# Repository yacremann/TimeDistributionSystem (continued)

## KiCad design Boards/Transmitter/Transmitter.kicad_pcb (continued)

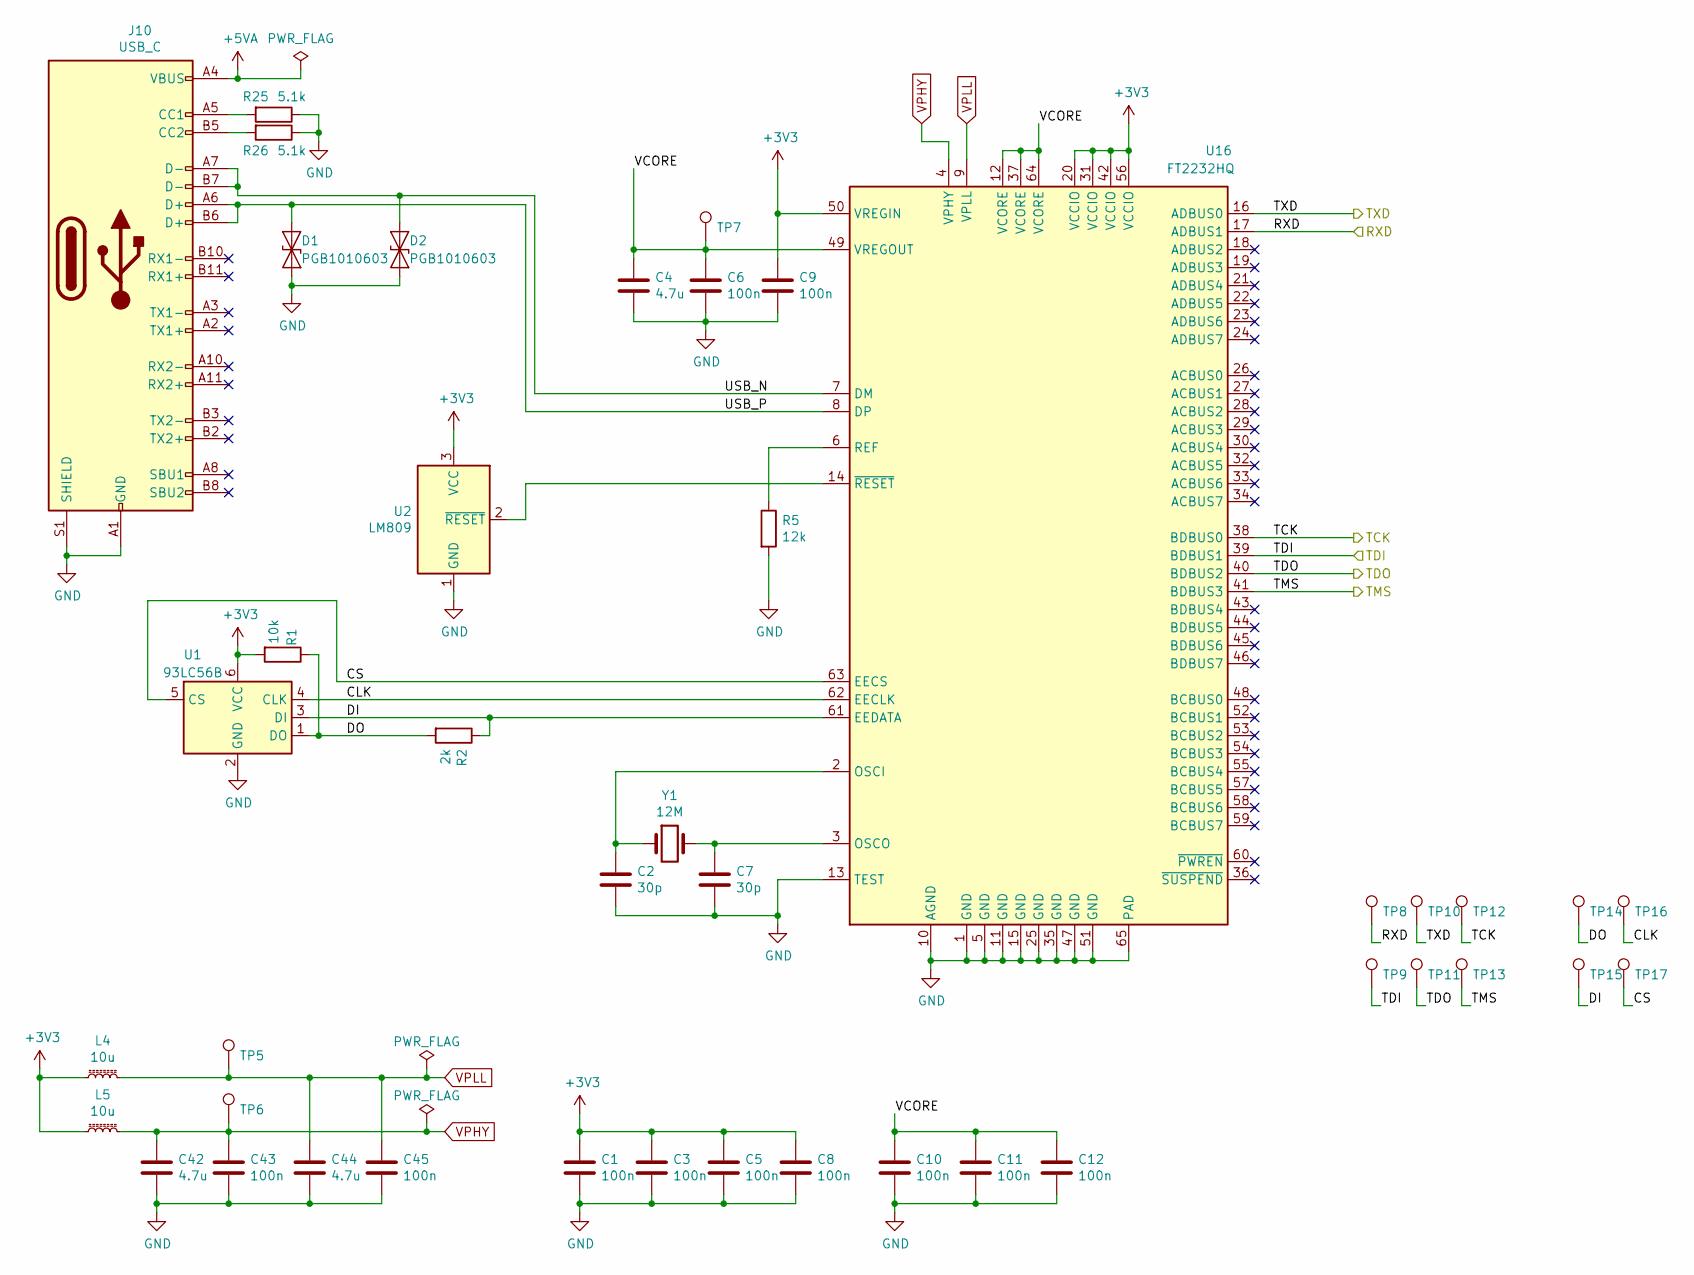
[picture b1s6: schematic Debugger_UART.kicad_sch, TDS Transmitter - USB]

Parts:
C1, C3, C5, C6, C8, C9, C10, C11, C12, C43, C45: 100n; C_0603_1608Metric
C2, C7: 30p; C_0603_1608Metric
C4, C42, C44: 4.7u; C_0603_1608Metric
D1, D2: PGB1010603; D_0603_1608Metric
J10: USB_C; USB_C_Receptacle_Amphenol_12401610E4-2A_CircularHoles
L4, L5: 10u; L_1008_2520Metric
R1: 10k; R_0603_1608Metric
R2: 2k; R_0603_1608Metric
R5: 12k; R_0603_1608Metric
R25, R26: 5.1k; R_0603_1608Metric
TP5, TP6, TP7, TP8, TP9, TP10, TP11, TP12, TP13, TP14, TP15, TP16, TP17: TestPoint; TestPoint_THTPad_D1.5mm_Drill0.7mm
U1: 93LC56B; SOT-23-6
U2: LM809; SOT-23
U16: FT2232HQ; QFN-64-1EP_9x9mm_P0.5mm_EP4.35x4.35mm
Y1: 12M; Crystal_SMD_5032-2Pin_5.0x3.2mm

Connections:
+3V3: C1.1, C3.1, C5.1, C8.1, C9.1, L4.1, L5.1, R1.2, U1.6 (VCC), U2.3 (VCC), U16.20 (VCCIO), U16.31 (VCCIO), U16.42 (VCCIO), U16.50 (VREGIN), U16.56 (VCCIO); also elsewhere on the board
+5VA: J10.A4 (VBUS), J10.A9 (VBUS), J10.B4 (VBUS), J10.B9 (VBUS); also elsewhere on the board
/Debugger_UART/CLK: TP16.1, U1.4 (CLK), U16.62 (EECLK)
/Debugger_UART/CS: TP17.1, U1.5 (CS), U16.63 (EECS)
/Debugger_UART/DI: R2.1, TP15.1, U1.3 (DI), U16.61 (EEDATA)
/Debugger_UART/DO: R1.1, R2.2, TP14.1, U1.1 (DO)
/Debugger_UART/RXD: TP8.1, U16.17 (ADBUS1); also elsewhere on the board
/Debugger_UART/TCK: TP12.1, U16.38 (BDBUS0); also elsewhere on the board
/Debugger_UART/TDI: TP9.1, U16.39 (BDBUS1); also elsewhere on the board
/Debugger_UART/TDO: TP11.1, U16.40 (BDBUS2); also elsewhere on the board
/Debugger_UART/TMS: TP13.1, U16.41 (BDBUS3); also elsewhere on the board
/Debugger_UART/USB_N: D2.1 (A1), J10.A7 (D-), J10.B7 (D-), U16.7 (DM)
/Debugger_UART/USB_P: D1.1 (A1), J10.A6 (D+), J10.B6 (D+), U16.8 (DP)
/Debugger_UART/VCORE: C4.1, C6.1, C10.1, C11.1, C12.1, TP7.1, U16.12 (VCORE), U16.37 (VCORE), U16.49 (VREGOUT), U16.64 (VCORE)
/FPGA_MRAM_Serializer/RXD: TP10.1, U16.16 (ADBUS0); also elsewhere on the board
GND: C1.2, C2.2, C3.2, C4.2, C5.2, C6.2, C7.2, C8.2, C9.2, C10.2, C11.2, C12.2, C42.2, C43.2, C44.2, C45.2, D1.2 (A2), D2.2 (A2), J10.A1 (GND), J10.A12 (GND), J10.B1 (GND), J10.B12 (GND), J10.S1 (SHIELD), R5.2, R25.1, R26.1, U1.2 (GND), U2.1 (GND), U16.1 (GND), U16.5 (GND), U16.10 (AGND), U16.11 (GND), U16.13 (TEST), U16.15 (GND), U16.25 (GND), U16.35 (GND), U16.47 (GND), U16.51 (GND), U16.65 (PAD); also elsewhere on the board
unnamed: C2.1, U16.2 (OSCI), Y1.1
unnamed: C7.1, U16.3 (OSCO), Y1.2
unnamed: J10.A5 (CC1), R25.2
unnamed: J10.B5 (CC2), R26.2
unnamed: R5.1, U16.6 (REF)
unnamed: U2.2 (~RESET), U16.14 (~RESET)
VPHY: C42.1, C43.1, L5.2, TP6.1, U16.4 (VPHY)
VPLL: C44.1, C45.1, L4.2, TP5.1, U16.9 (VPLL)

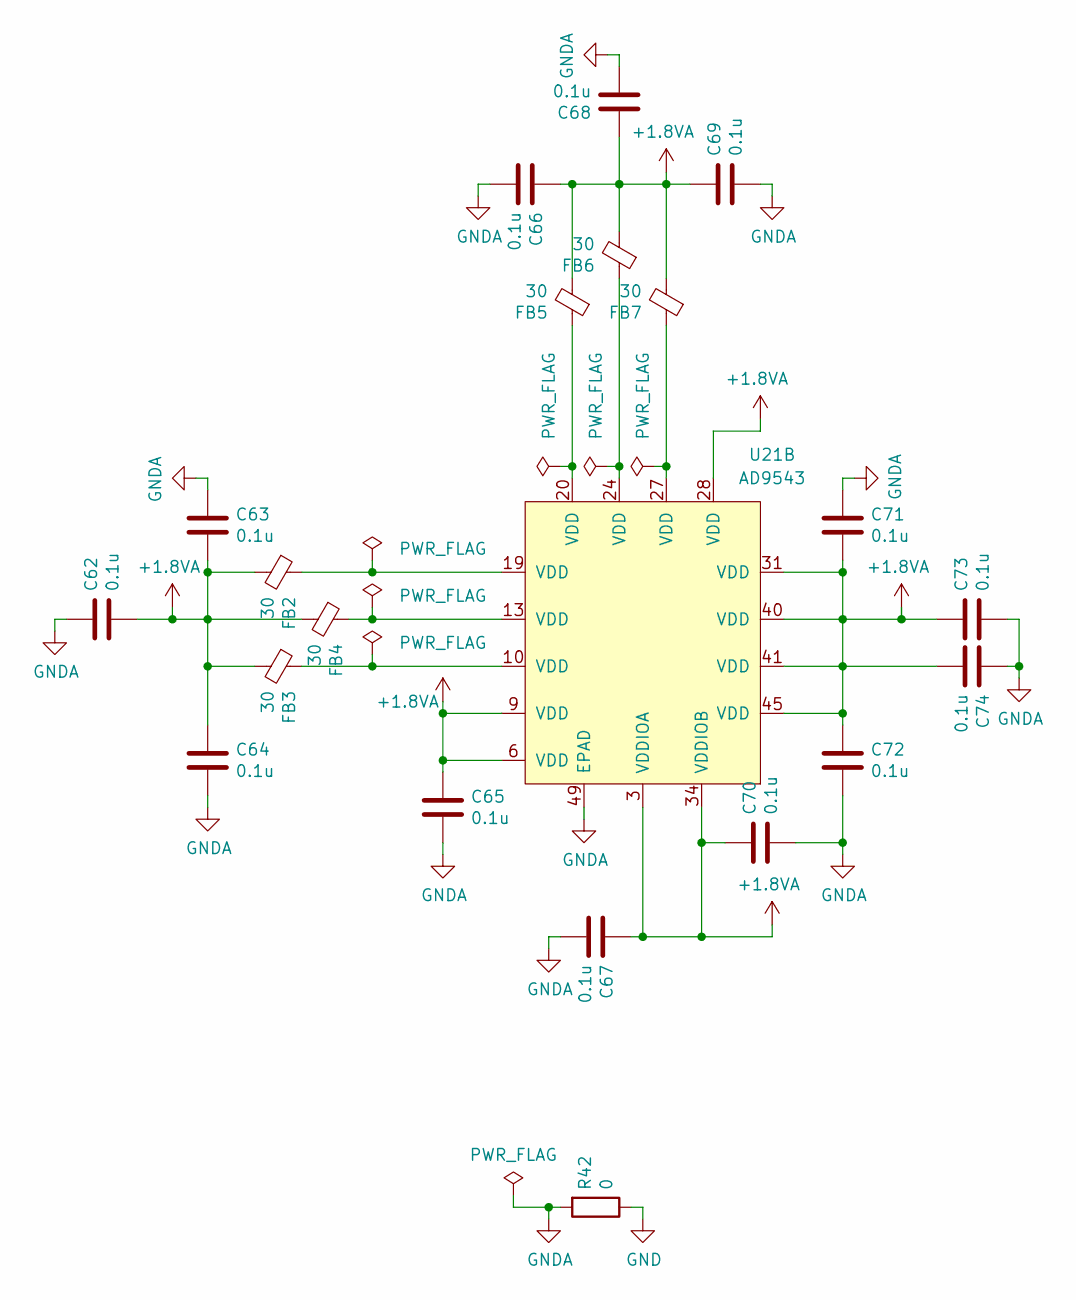
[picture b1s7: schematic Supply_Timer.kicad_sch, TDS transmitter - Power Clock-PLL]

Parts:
C62, C63, C64, C65, C66, C67, C68, C69, C70, C71, C72, C73, C74: 0.1u; C_0402_1005Metric
FB2, FB3, FB4, FB5, FB6, FB7: 30; L_0402_1005Metric
R42: 0; R_0603_1608Metric
U21: AD9543; LFCSP-48-1EP_7x7mm_P0.5mm_EP4.1x4.1mm

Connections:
+1V0: C62.1, C63.1, C64.2, C65.2, C66.2, C67.2, C68.2, C69.2, C70.2, C71.1, C72.2, C73.2, C74.1, FB2.2, FB3.2, FB4.2, FB5.2, FB6.2, FB7.2, U21.3 (VDDIOA), U21.6 (VDD), U21.9 (VDD), U21.28 (VDD), U21.31 (VDD), U21.34 (VDDIOB), U21.40 (VDD), U21.41 (VDD), U21.45 (VDD); also elsewhere on the board
GND: R42.1; also elsewhere on the board
GNDA: C62.2, C63.2, C64.1, C65.1, C66.1, C67.1, C68.1, C69.1, C70.1, C71.2, C72.1, C73.1, C74.2, R42.2, U21.49 (EPAD); also elsewhere on the board
unnamed: FB2.1, U21.19 (VDD)
unnamed: FB3.1, U21.10 (VDD)
unnamed: FB4.1, U21.13 (VDD)
unnamed: FB5.1, U21.20 (VDD)
unnamed: FB6.1, U21.24 (VDD)
unnamed: FB7.1, U21.27 (VDD)

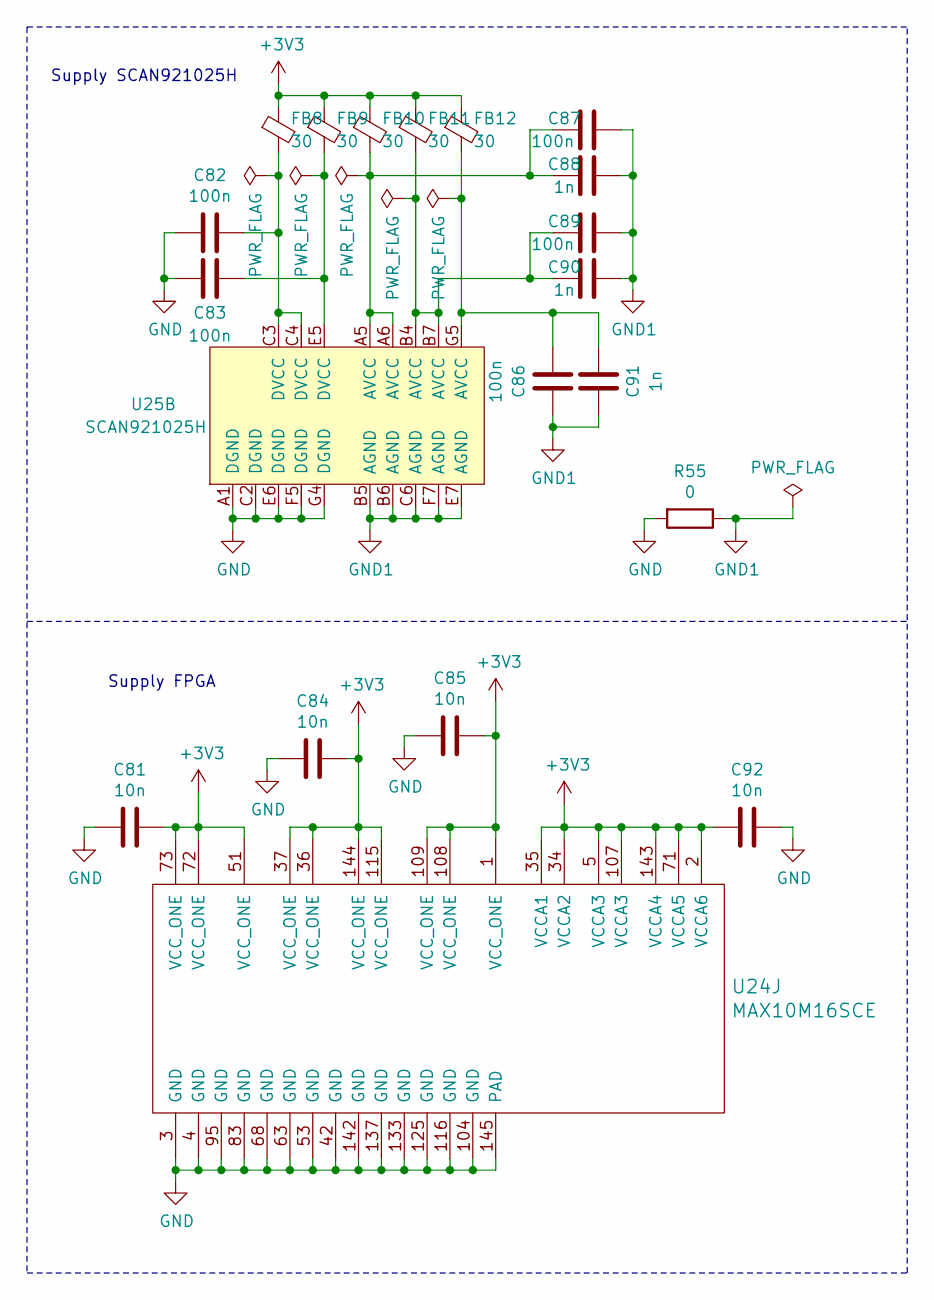
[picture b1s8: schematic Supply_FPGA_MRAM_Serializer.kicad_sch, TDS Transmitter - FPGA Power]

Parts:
C81, C84, C85, C92: 10n; C_0603_1608Metric
C82, C83, C86, C87, C89: 100n; C_0402_1005Metric
C88, C90, C91: 1n; C_0402_1005Metric
FB8, FB9, FB10, FB11, FB12: 30; L_0402_1005Metric
R55: 0; R_0603_1608Metric
U24: MAX10M16SCE; EQFP_144
U25: SCAN921025H; BGA-49_7x7_7.0x7.0mm

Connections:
+3V3: C81.1, C84.1, C85.1, C92.2, FB8.1, FB9.1, FB10.1, FB11.1, FB12.1, U24.1 (VCC_ONE), U24.2 (VCCA6), U24.5 (VCCA3), U24.34 (VCCA2), U24.35 (VCCA1), U24.36 (VCC_ONE), U24.37 (VCC_ONE), U24.51 (VCC_ONE), U24.71 (VCCA5), U24.72 (VCC_ONE), U24.73 (VCC_ONE), U24.107 (VCCA3), U24.108 (VCC_ONE), U24.109 (VCC_ONE), U24.115 (VCC_ONE), U24.143 (VCCA4), U24.144 (VCC_ONE); also elsewhere on the board
GND: C81.2, C82.2, C83.2, C84.2, C85.2, C92.1, R55.2, U24.3 (GND), U24.4 (GND), U24.42 (GND), U24.53 (GND), U24.63 (GND), U24.68 (GND), U24.83 (GND), U24.95 (GND), U24.104 (GND), U24.116 (GND), U24.125 (GND), U24.133 (GND), U24.137 (GND), U24.142 (GND), U24.145 (PAD), U25.A1 (DGND), U25.C2 (DGND), U25.E6 (DGND), U25.F5 (DGND), U25.G4 (DGND); also elsewhere on the board
GND1: C86.1, C87.2, C88.1, C89.2, C90.2, C91.2, R55.1, U25.B5 (AGND), U25.B6 (AGND), U25.C6 (AGND), U25.E7 (AGND), U25.F7 (AGND)
unnamed: C82.1, FB8.2, U25.C3 (DVCC), U25.C4 (DVCC)
unnamed: C83.1, FB9.2, U25.E5 (DVCC)
unnamed: C86.2, C91.1, FB12.2, U25.G5 (AVCC)
unnamed: C87.1, C88.2, FB10.2, U25.A5 (AVCC), U25.A6 (AVCC)
unnamed: C89.1, C90.1, FB11.2, U25.B4 (AVCC), U25.B7 (AVCC)

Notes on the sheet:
Supply FPGA
Supply SCAN921025H

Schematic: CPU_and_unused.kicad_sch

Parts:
C52, C93, C94, C95: 100n; C_0603_1608Metric
FB13: 30; L_0402_1005Metric
J15: Conn_01x14; PinHeader_1x14_P2.54mm_Vertical
J16: LED_1; 3.81mm_2_pos
J17: LED_2; 3.81mm_2_pos
J18: LED_3; 3.81mm_2_pos
Q1, Q2, Q3: BSS123; SOT-23
R56, R57, R58: 0; R_0603_1608Metric
U24: MAX10M16SCE; EQFP_144

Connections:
+1V0: FB13.1; also elsewhere on the board
+3V3: C93.1, C94.2, C95.1, J15.1, R56.1, R57.1, R58.1, U24.9 (VCCIO1A), U24.23 (VCCIO1B), U24.40 (VCCIO3), U24.49 (VCCIO3), U24.117 (VCCIO7), U24.128 (VCCIO8), U24.139 (VCCIO8); also elsewhere on the board
/Clock/M0: U24.85 (IO); also elsewhere on the board
/Clock/M1: U24.81 (IO); also elsewhere on the board
/Clock/M2: U24.78 (IO); also elsewhere on the board
/Debugger_UART/RXD: U24.39 (IO); also elsewhere on the board
/Debugger_UART/TCK: U24.46 (IO); also elsewhere on the board
/Debugger_UART/TDI: U24.45 (IO); also elsewhere on the board
/Debugger_UART/TDO: U24.44 (IO); also elsewhere on the board
/Debugger_UART/TMS: U24.43 (IO); also elsewhere on the board
/FPGA_MRAM_Serializer/CPU_and_unused/LED_1: Q1.1 (G), U24.50 (IO)
/FPGA_MRAM_Serializer/CPU_and_unused/LED_2: Q2.1 (G), U24.52 (IO)
/FPGA_MRAM_Serializer/CPU_and_unused/LED_3: Q3.1 (G), U24.54 (IO)
/FPGA_MRAM_Serializer/RXD: U24.38 (IO); also elsewhere on the board
/FPGA_MRAM_Serializer/SPI_Timer_CSB: U24.77 (IO/RDN); also elsewhere on the board
/FPGA_MRAM_Serializer/SPI_Timer_SCLK: U24.75 (IO/RUP); also elsewhere on the board
/FPGA_MRAM_Serializer/SPI_Timer_SDIO: U24.76 (IO); also elsewhere on the board
/FPGA_MRAM_Serializer/SPI_Timer_SDO: U24.74 (IO); also elsewhere on the board
/Slow_Pulse_ID: U24.60 (IO); also elsewhere on the board
GND: C52.2, C93.2, C94.1, C95.2, J15.14, Q1.2 (S), Q2.2 (S), Q3.2 (S); also elsewhere on the board
unnamed: C52.1, FB13.2, U24.82 (VCCIO5)
unnamed: J15.2, U24.114 (IO)
unnamed: J15.3, U24.118 (IO)
unnamed: J15.4, U24.119 (IO)
unnamed: J15.5, U24.120 (IO)
unnamed: J15.6, U24.124 (IO)
unnamed: J15.7, U24.127 (IO)
unnamed: J15.8, U24.130 (IO)
unnamed: J15.9, U24.131 (IO)
unnamed: J15.10, U24.132 (IO)
unnamed: J15.11, U24.135 (IO)
unnamed: J15.12, U24.140 (IO)
unnamed: J15.13, U24.141 (IO)
unnamed: J16.1, R56.2
unnamed: J16.2, Q1.3 (D)
unnamed: J17.1, R57.2
unnamed: J17.2, Q2.3 (D)
unnamed: J18.1, R58.2
unnamed: J18.2, Q3.3 (D)
~RESET: U24.86 (IO); also elsewhere on the board

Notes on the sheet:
AD9543 connections Reset recieve
CPU connection
2-3 LEDs herausführen und allgemein noch pins vom fpga ausführen

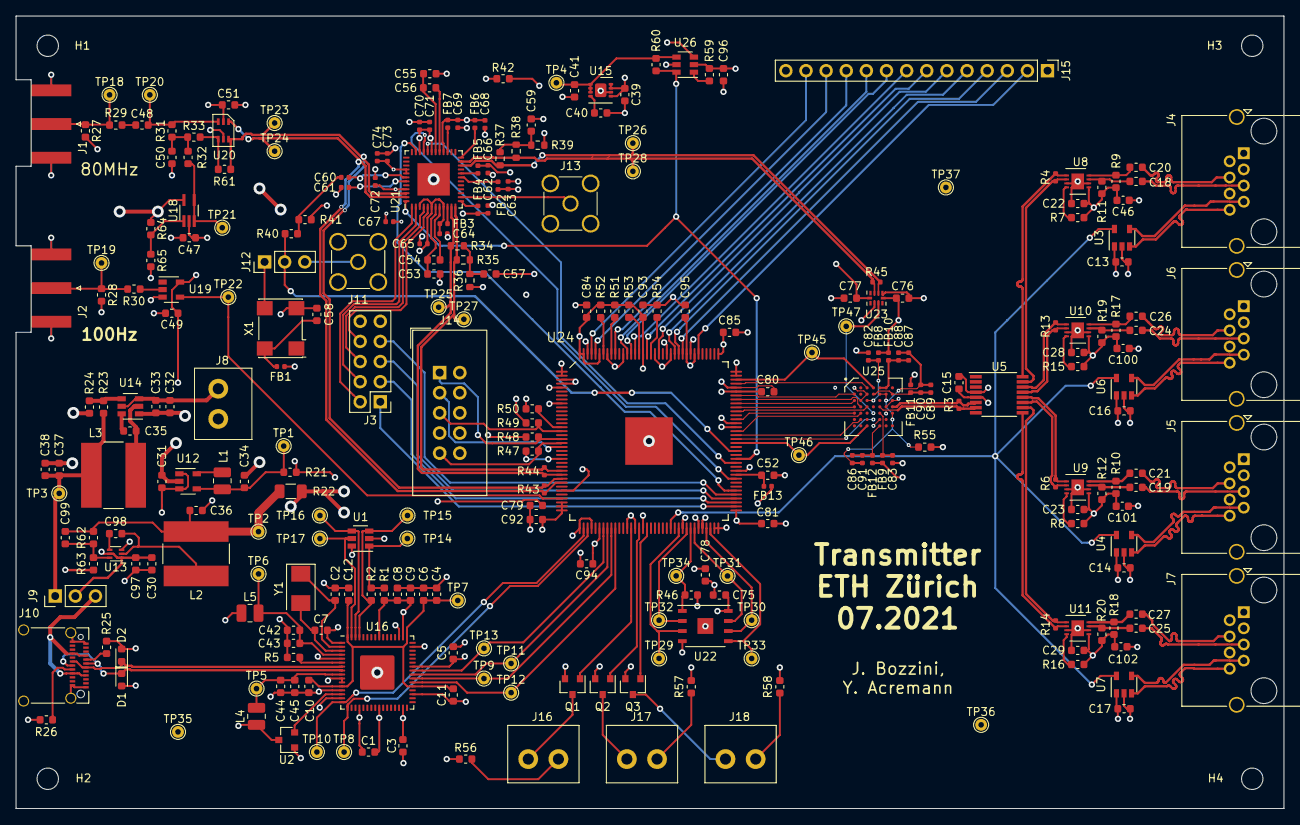
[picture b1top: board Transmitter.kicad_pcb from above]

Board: 4 copper layers, 160.0 x 100.0 mm, 279 parts (0 on the bottom side), 184 nets.

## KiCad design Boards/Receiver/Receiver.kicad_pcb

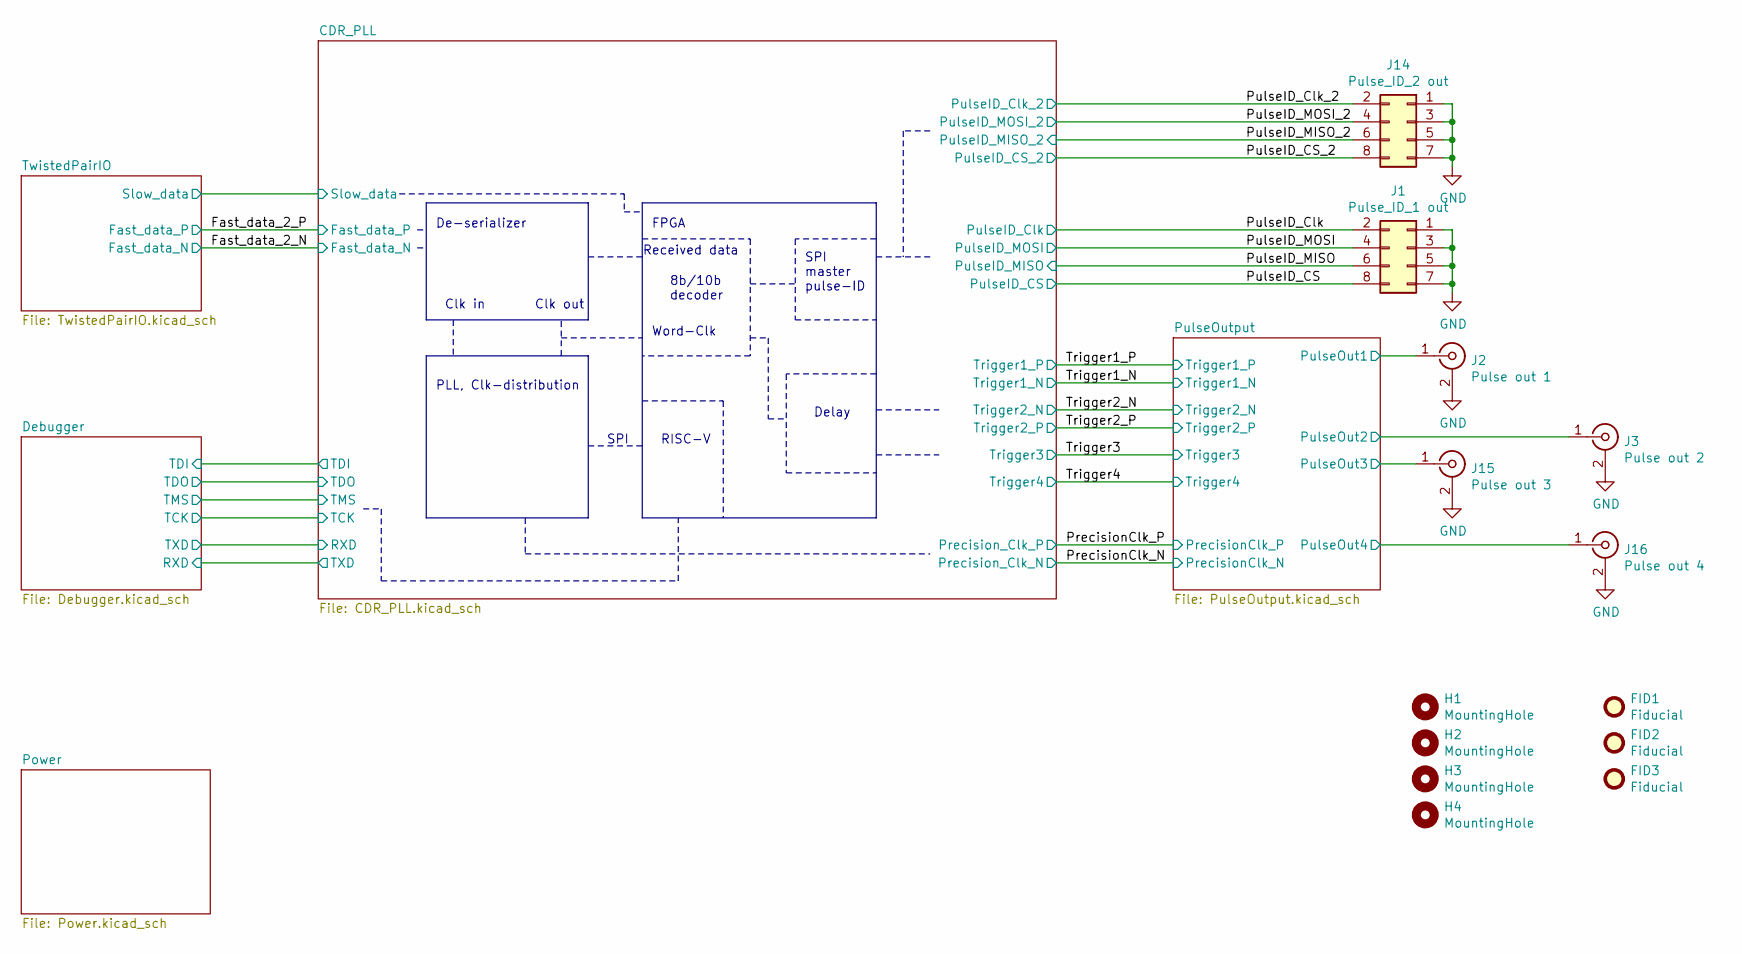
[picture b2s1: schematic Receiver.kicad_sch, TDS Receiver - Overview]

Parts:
FID1, FID2, FID3: Fiducial; Fiducial_0.5mm_Mask1.5mm
H1, H2, H3, H4: MountingHole; MountingHole_2.7mm_M2.5
J1: Pulse_ID_1 out; PinHeader_2x04_P2.54mm_Vertical
J2: Pulse out 1; SMA_Amphenol_132289_EdgeMount
J3: Pulse out 2; SMA_Amphenol_132289_EdgeMount
J14: Pulse_ID_2 out; PinHeader_2x04_P2.54mm_Vertical
J15: Pulse out 3; SMA_Amphenol_132289_EdgeMount
J16: Pulse out 4; SMA_Amphenol_132289_EdgeMount

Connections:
/PulseID_CS: J1.8; also elsewhere on the board
/PulseID_CS_2: J14.8; also elsewhere on the board
/PulseID_Clk: J1.2; also elsewhere on the board
/PulseID_Clk_2: J14.2; also elsewhere on the board
/PulseID_MISO: J1.6; also elsewhere on the board
/PulseID_MISO_2: J14.6; also elsewhere on the board
/PulseID_MOSI: J1.4; also elsewhere on the board
/PulseID_MOSI_2: J14.4; also elsewhere on the board
/PulseOutput/PulseOut1: J2.1 (In); also elsewhere on the board
/PulseOutput/PulseOut2: J3.1 (In); also elsewhere on the board
/PulseOutput/PulseOut3: J15.1 (In); also elsewhere on the board
/PulseOutput/PulseOut4: J16.1 (In); also elsewhere on the board
GND: J1.1, J1.3, J1.5, J1.7, J2.2 (Ext), J3.2 (Ext), J14.1, J14.3, J14.5, J14.7, J15.2 (Ext), J16.2 (Ext); also elsewhere on the board

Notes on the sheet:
Clk in
SPI master pulse-ID
De-serializer
Delay
8b/10b decoder
PLL, Clk-distribution
Word-Clk
SPI
Received data
Clk out
RISC-V
FPGA

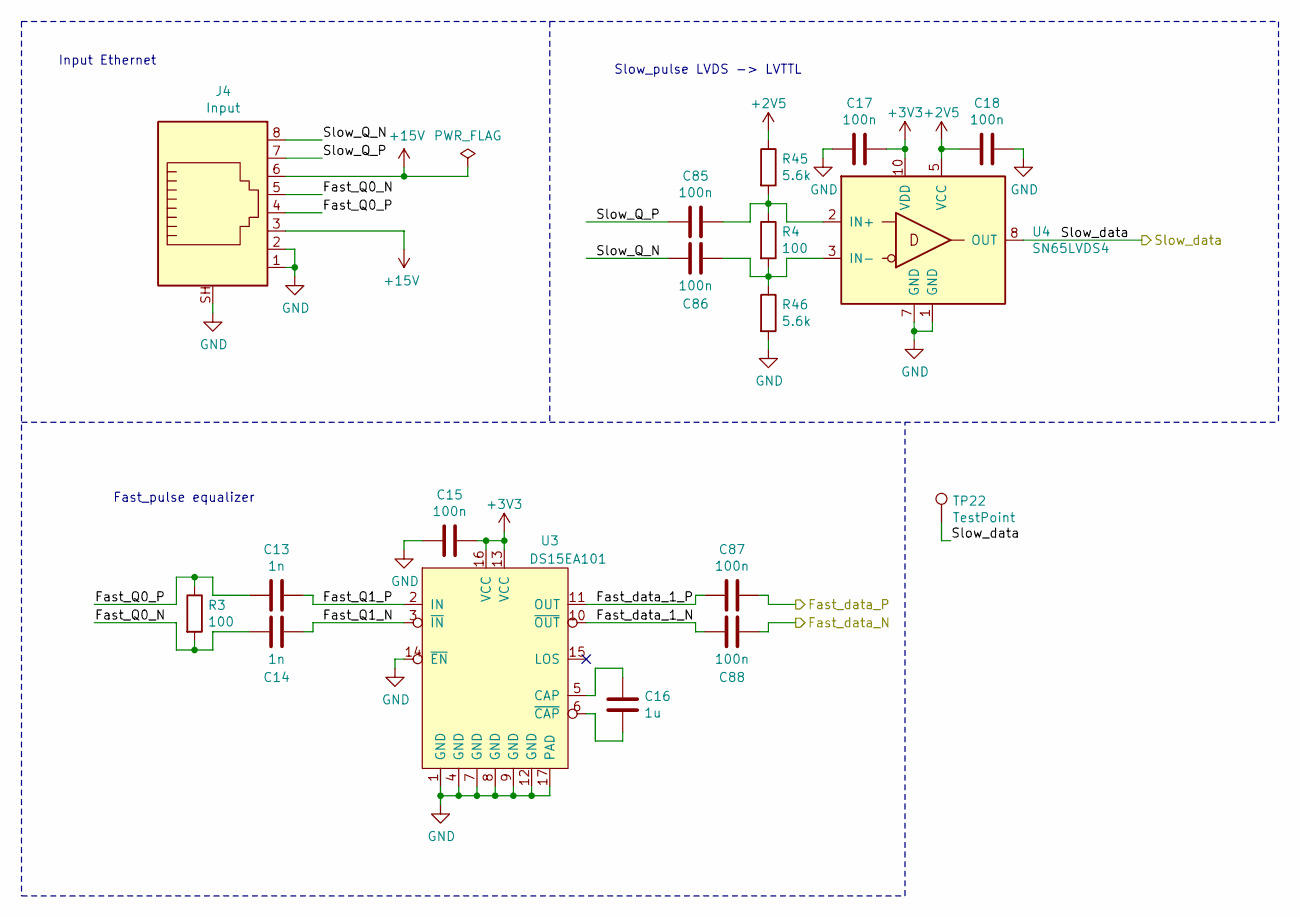
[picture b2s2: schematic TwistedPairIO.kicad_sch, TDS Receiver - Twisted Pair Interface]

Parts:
C13, C14: 1n; C_0402_1005Metric
C15, C17, C18: 100n; C_0603_1608Metric
C16: 1u; C_0603_1608Metric
C85, C86, C87, C88: 100n; C_0402_1005Metric
J4: Input; RJ45_Amphenol_RJHSE5380
R3, R4: 100; R_0603_1608Metric
R45, R46: 5.6k; R_0603_1608Metric
TP22: TestPoint; TestPoint_THTPad_D1.5mm_Drill0.7mm
U3: DS15EA101; WQFN-16-1EP_4x4mm_P0.5mm_EP2.6x2.6mm
U4: SN65LVDS4; Texas_R-PUQFN-N10

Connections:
+2V5: C18.2, R45.1, U4.5 (VCC); also elsewhere on the board
+3V3: C15.1, C17.1, U3.13 (VCC), U3.16 (VCC), U4.10 (VDD); also elsewhere on the board
+15V: J4.3, J4.6; also elsewhere on the board
/CDR_PLL/Slow_data: TP22.1, U4.8 (OUT); also elsewhere on the board
/Fast_data_2_N: C88.1; also elsewhere on the board
/Fast_data_2_P: C87.1; also elsewhere on the board
/TwistedPairIO/Fast_Q0_N: C14.1, J4.5, R3.2
/TwistedPairIO/Fast_Q0_P: C13.2, J4.4, R3.1
/TwistedPairIO/Fast_Q1_N: C14.2, U3.3 (~IN)
/TwistedPairIO/Fast_Q1_P: C13.1, U3.2 (IN)
/TwistedPairIO/Fast_data_1_N: C88.2, U3.10 (~OUT)
/TwistedPairIO/Fast_data_1_P: C87.2, U3.11 (OUT)
/TwistedPairIO/Slow_Q_N: C86.2, J4.8
/TwistedPairIO/Slow_Q_P: C85.2, J4.7
GND: C15.2, C17.2, C18.1, J4.1, J4.2, J4.SH, R46.2, U3.1 (GND), U3.4 (GND), U3.7 (GND), U3.8 (GND), U3.9 (GND), U3.12 (GND), U3.14 (~EN), U3.17 (PAD), U4.1 (GND), U4.7 (GND); also elsewhere on the board
unnamed: C16.1, U3.5 (CAP)
unnamed: C16.2, U3.6 (~CAP)
unnamed: C85.1, R4.1, R45.2, U4.2 (IN+)
unnamed: C86.1, R4.2, R46.1, U4.3 (IN-)

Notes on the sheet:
Input Ethernet
Fast_pulse equalizer
Slow_pulse LVDS -> LVTTL

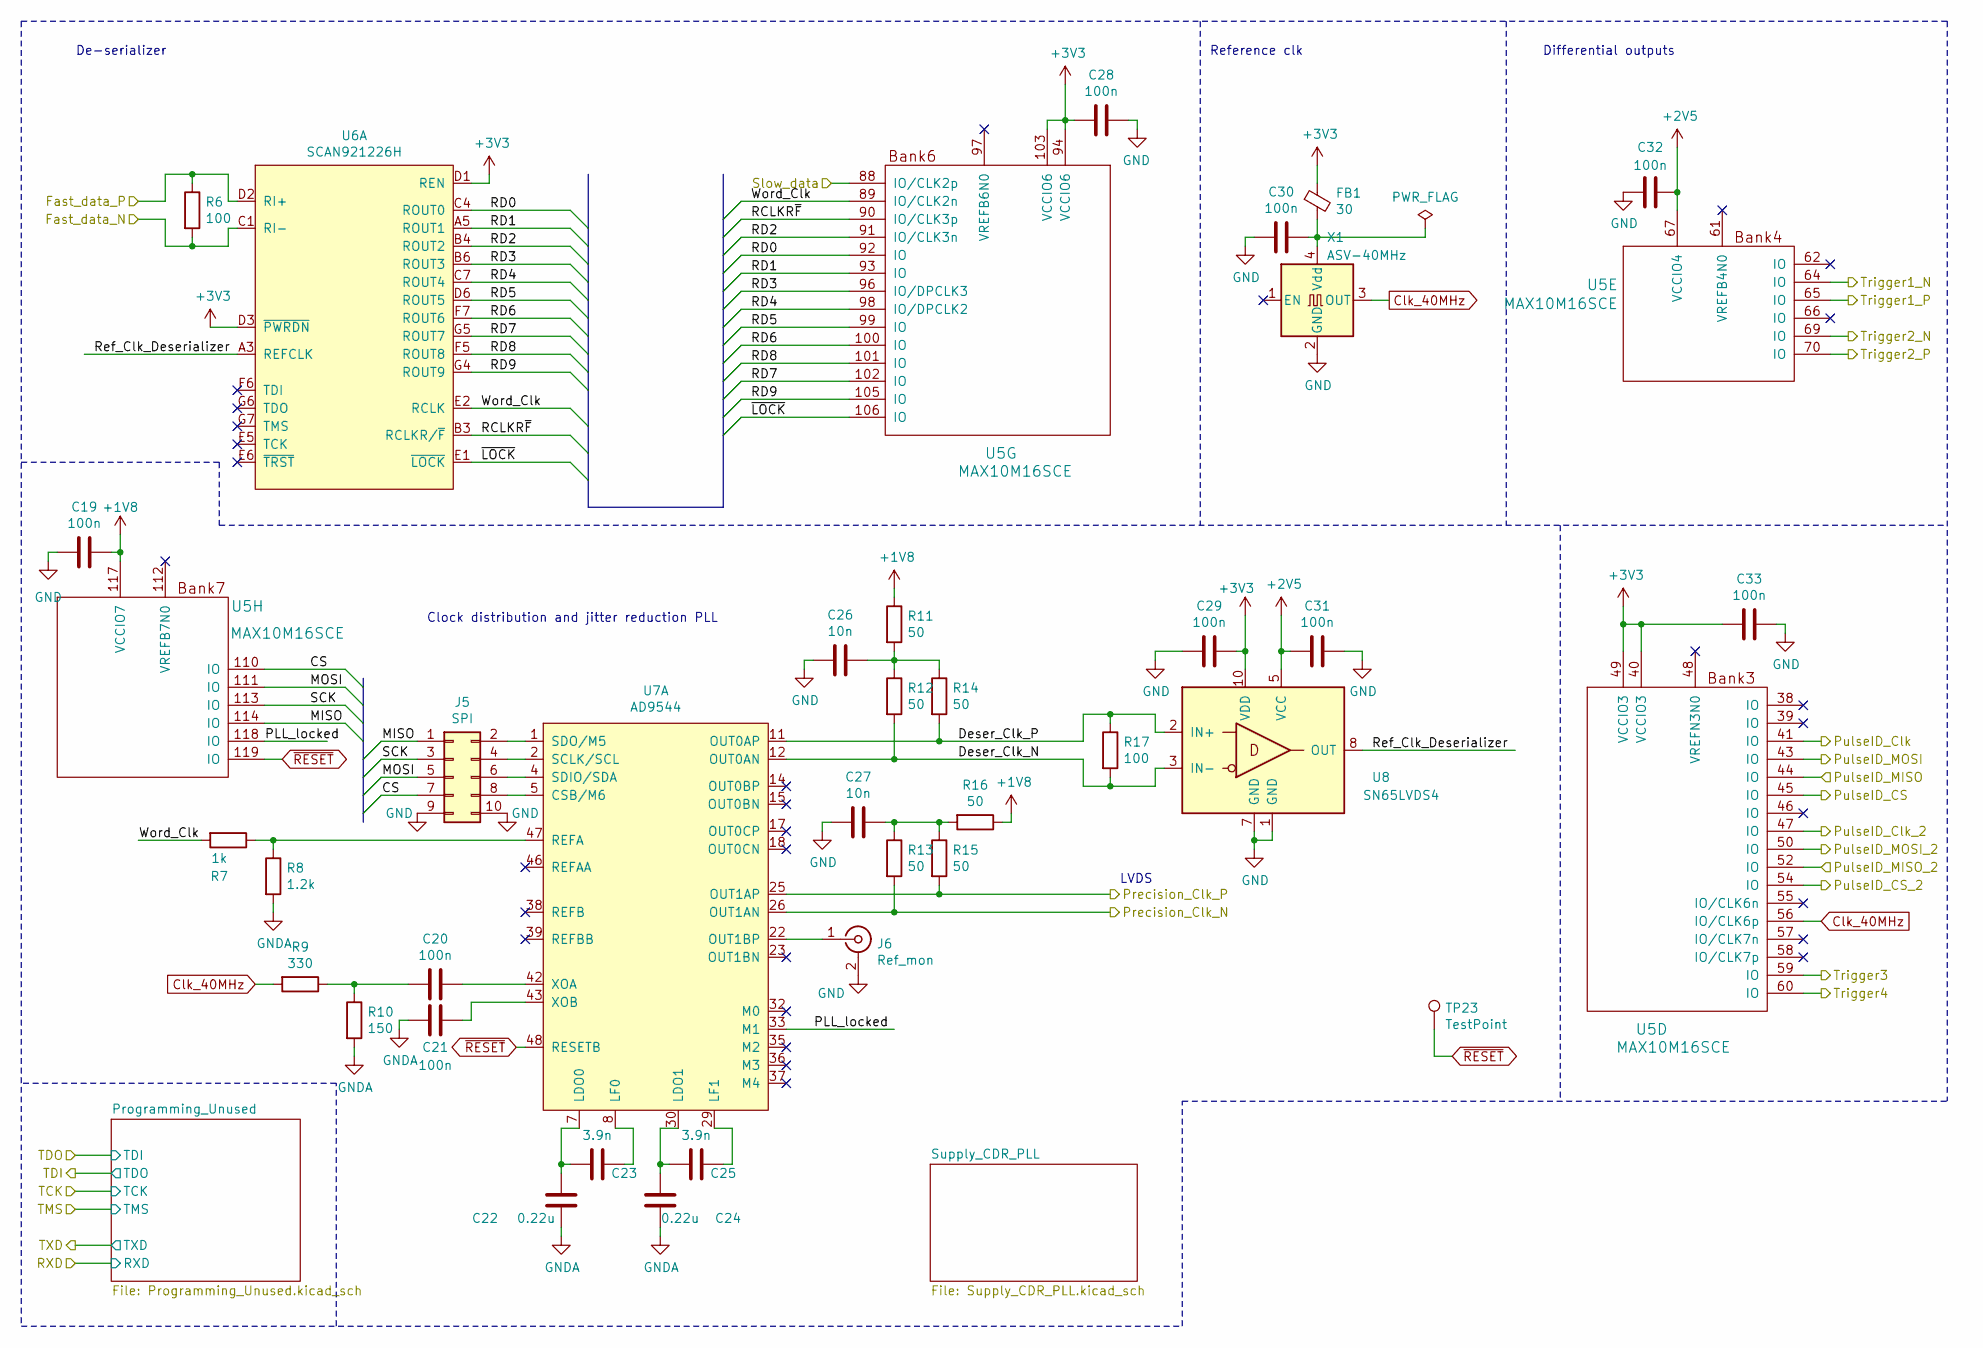
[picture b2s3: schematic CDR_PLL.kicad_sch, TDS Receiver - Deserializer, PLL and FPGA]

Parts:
C19, C28, C29, C30, C31, C32, C33: 100n; C_0603_1608Metric
C20, C21: 100n; C_0402_1005Metric
C22, C24: 0.22u; C_0603_1608Metric
C23, C25: 3.9n; C_0603_1608Metric
C26, C27: 10n; C_0603_1608Metric
FB1: 30; L_0402_1005Metric
J5: SPI; PinHeader_2x05_P2.54mm_Vertical
J6: Ref_mon; SMA_Amphenol_901-144_Vertical
R6, R17: 100; R_0603_1608Metric
R7: 1k; R_0603_1608Metric
R8: 1.2k; R_0603_1608Metric
R9: 330; R_0603_1608Metric
R10: 150; R_0603_1608Metric
R11, R12, R13, R14, R15, R16: 50; R_0603_1608Metric
TP23: TestPoint; TestPoint_THTPad_D1.5mm_Drill0.7mm
U5: MAX10M16SCE; EQFP_144
U6: SCAN921226H; BGA-49_7x7_7.0x7.0mm
U7: AD9544; LFCSP-48-1EP_7x7mm_P0.5mm_EP4.1x4.1mm
U8: SN65LVDS4; Texas_R-PUQFN-N10
X1: ASV-40MHz; Oscillator_SMD_Abracon_ASV-4Pin_7.0x5.1mm

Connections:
+1V8: C19.1, R11.1, R16.1, U5.117 (VCCIO7); also elsewhere on the board
+2V5: C31.2, C32.1, U5.67 (VCCIO4), U8.5 (VCC); also elsewhere on the board
+3V3: C28.2, C29.1, C33.2, FB1.1, U5.40 (VCCIO3), U5.49 (VCCIO3), U5.94 (VCCIO6), U5.103 (VCCIO6), U6.D1 (REN), U6.D3 (~PWRDN), U8.10 (VDD); also elsewhere on the board
/CDR_PLL/CS: J5.7, U5.110 (IO)
/CDR_PLL/Deser_Clk_N: R12.2, R17.2, U7.12 (OUT0AN), U8.3 (IN-)
/CDR_PLL/Deser_Clk_P: R14.2, R17.1, U7.11 (OUT0AP), U8.2 (IN+)
/CDR_PLL/MISO: J5.1, U5.114 (IO)
/CDR_PLL/MOSI: J5.5, U5.111 (IO)
/CDR_PLL/PLL_locked: U5.118 (IO), U7.33 (M1)
/CDR_PLL/RCLKR~F: U5.90 (IO/CLK3p), U6.B3 (RCLKR/~F)
/CDR_PLL/RD0: U5.92 (IO), U6.C4 (ROUT0)
/CDR_PLL/RD1: U5.93 (IO), U6.A5 (ROUT1)
/CDR_PLL/RD2: U5.91 (IO/CLK3n), U6.B4 (ROUT2)
/CDR_PLL/RD3: U5.96 (IO/DPCLK3), U6.B6 (ROUT3)
/CDR_PLL/RD4: U5.98 (IO/DPCLK2), U6.C7 (ROUT4)
/CDR_PLL/RD5: U5.99 (IO), U6.D6 (ROUT5)
/CDR_PLL/RD6: U5.100 (IO), U6.F7 (ROUT6)
/CDR_PLL/RD7: U5.102 (IO), U6.G5 (ROUT7)
/CDR_PLL/RD8: U5.101 (IO), U6.F5 (ROUT8)
/CDR_PLL/RD9: U5.105 (IO), U6.G4 (ROUT9)
/CDR_PLL/Ref_Clk_Deserializer: U6.A3 (REFCLK), U8.8 (OUT)
/CDR_PLL/SCK: J5.3, U5.113 (IO)
/CDR_PLL/Slow_data: U5.88 (IO/CLK2p); also elsewhere on the board
/CDR_PLL/Word_Clk: R7.2, U5.89 (IO/CLK2n), U6.E2 (RCLK)
/CDR_PLL/~LOCK: U5.106 (IO), U6.E1 (~LOCK)
/Fast_data_2_N: R6.2, U6.C1 (RI-); also elsewhere on the board
/Fast_data_2_P: R6.1, U6.D2 (RI+); also elsewhere on the board
/PrecisionClk_N: R13.2, U7.26 (OUT1AN); also elsewhere on the board
/PrecisionClk_P: R15.2, U7.25 (OUT1AP); also elsewhere on the board
/PulseID_CS: U5.45 (IO); also elsewhere on the board
/PulseID_CS_2: U5.54 (IO); also elsewhere on the board
/PulseID_Clk: U5.41 (IO); also elsewhere on the board
/PulseID_Clk_2: U5.47 (IO); also elsewhere on the board
/PulseID_MISO: U5.44 (IO); also elsewhere on the board
/PulseID_MISO_2: U5.52 (IO); also elsewhere on the board
/PulseID_MOSI: U5.43 (IO); also elsewhere on the board
/PulseID_MOSI_2: U5.50 (IO); also elsewhere on the board
/Trigger1_N: U5.64 (IO); also elsewhere on the board
/Trigger1_P: U5.65 (IO); also elsewhere on the board
/Trigger2_N: U5.69 (IO); also elsewhere on the board
/Trigger2_P: U5.70 (IO); also elsewhere on the board
/Trigger3: U5.59 (IO); also elsewhere on the board
/Trigger4: U5.60 (IO); also elsewhere on the board
Clk_40MHz: R9.2, U5.56 (IO/CLK6p), X1.3 (OUT); also elsewhere on the board
GND: C19.2, C26.2, C27.2, C28.1, C29.2, C30.2, C31.1, C32.2, C33.1, J5.9, J5.10, J6.2 (Ext), U8.1 (GND), U8.7 (GND), X1.2 (GND); also elsewhere on the board
GNDA: C21.2, C22.2, C24.2, R8.2, R10.2; also elsewhere on the board
unnamed: C20.1, U7.42 (XOA)
unnamed: C20.2, R9.1, R10.1
unnamed: C21.1, U7.43 (XOB)
unnamed: C22.1, C23.2, U7.7 (LDO0)
unnamed: C23.1, U7.8 (LF0)
unnamed: C24.1, C25.2, U7.30 (LDO1)
unnamed: C25.1, U7.29 (LF1)
unnamed: C26.1, R11.2, R12.1, R14.1
unnamed: C27.1, R13.1, R15.1, R16.2
unnamed: C30.1, FB1.2, X1.4 (Vdd)
unnamed: J5.2, U7.1 (SDO/M5)
unnamed: J5.4, U7.2 (SCLK/SCL)
unnamed: J5.6, U7.4 (SDIO/SDA)
unnamed: J5.8, U7.5 (CSB/M6)
unnamed: J6.1 (In), U7.22 (OUT1BP)
unnamed: R7.1, R8.1, U7.47 (REFA)
~RESET: TP23.1, U5.119 (IO), U7.48 (RESETB)

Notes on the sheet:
De-serializer
Clock distribution and jitter reduction PLL
Reference clk
Differential outputs
LVDS
